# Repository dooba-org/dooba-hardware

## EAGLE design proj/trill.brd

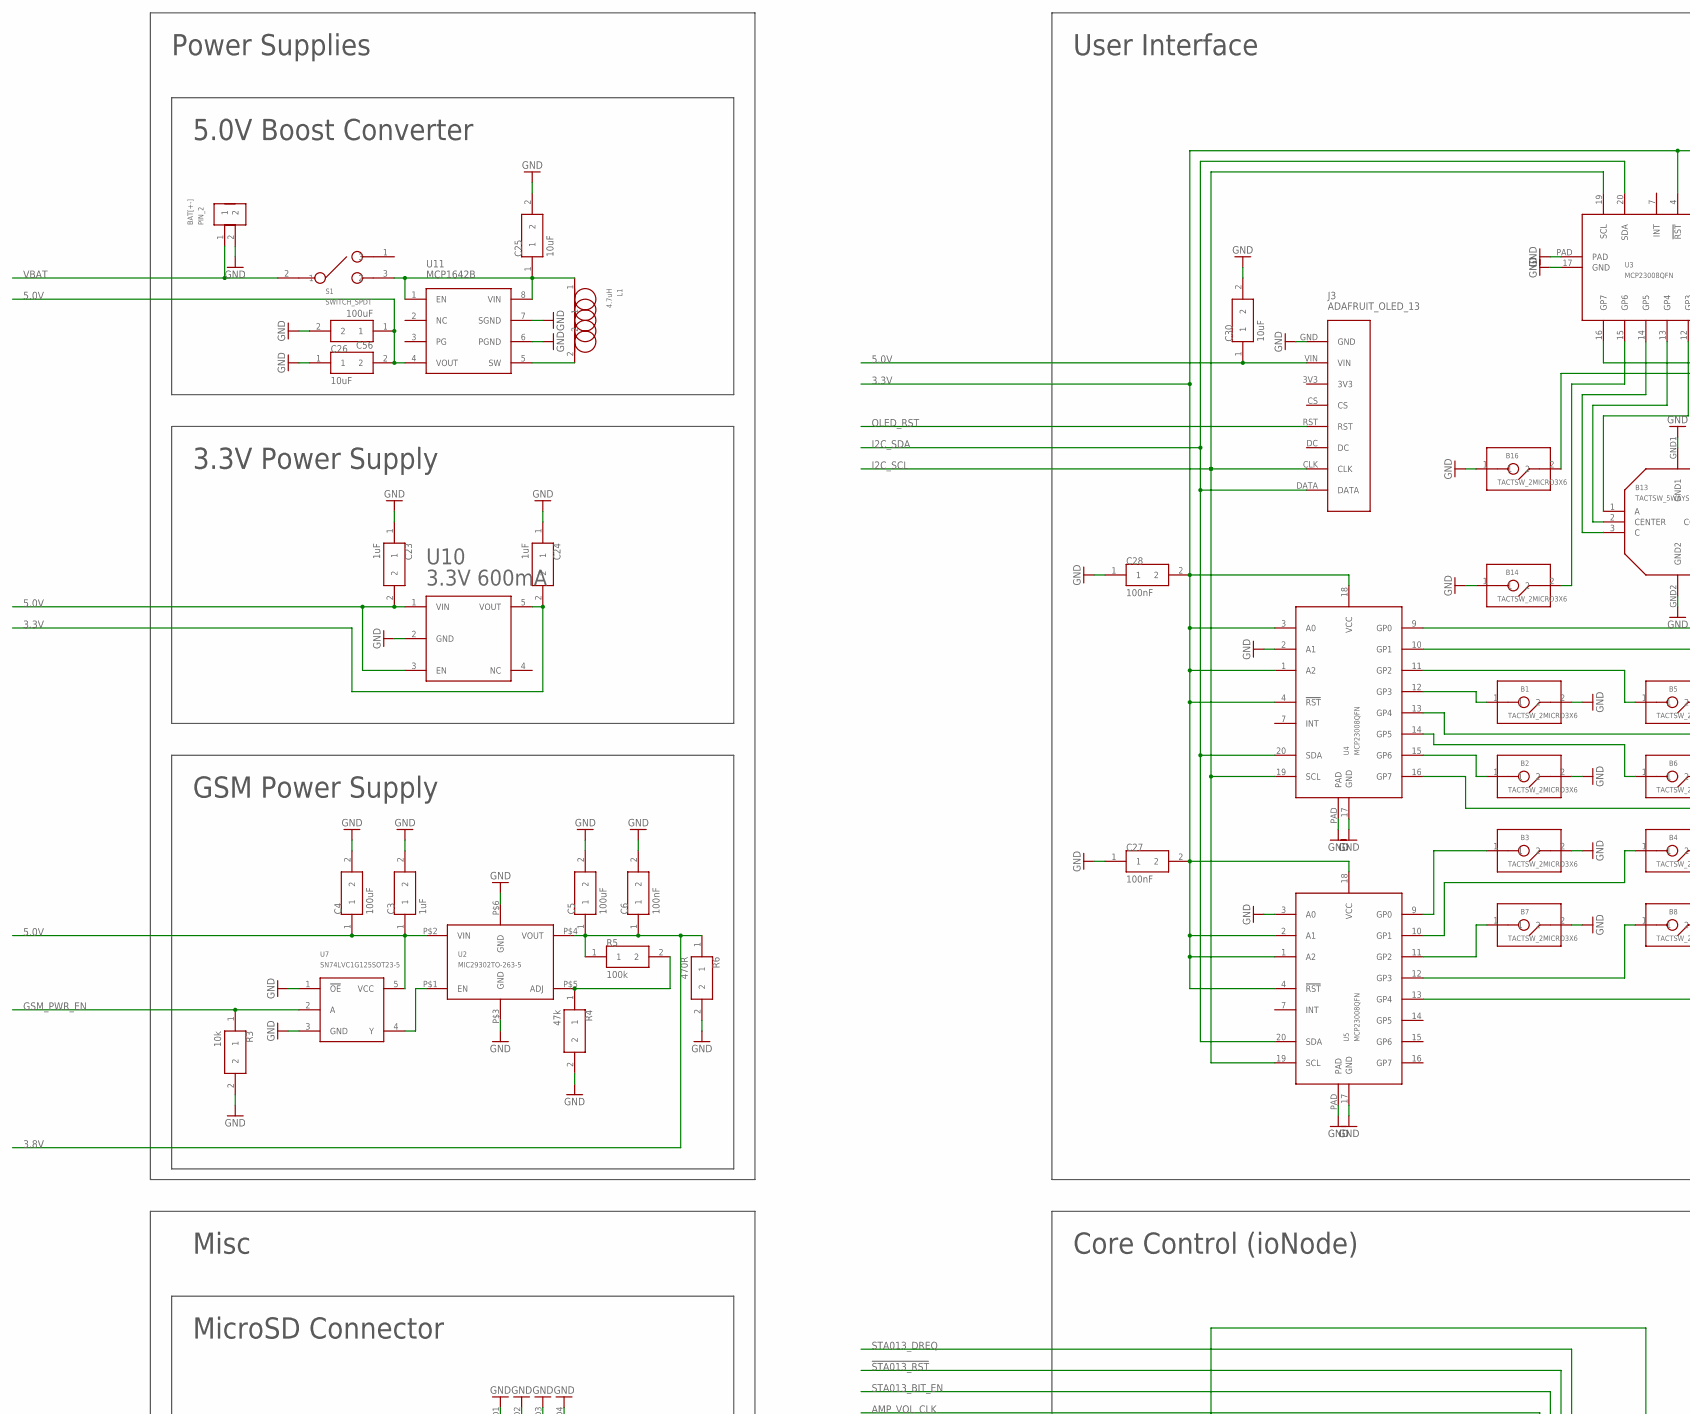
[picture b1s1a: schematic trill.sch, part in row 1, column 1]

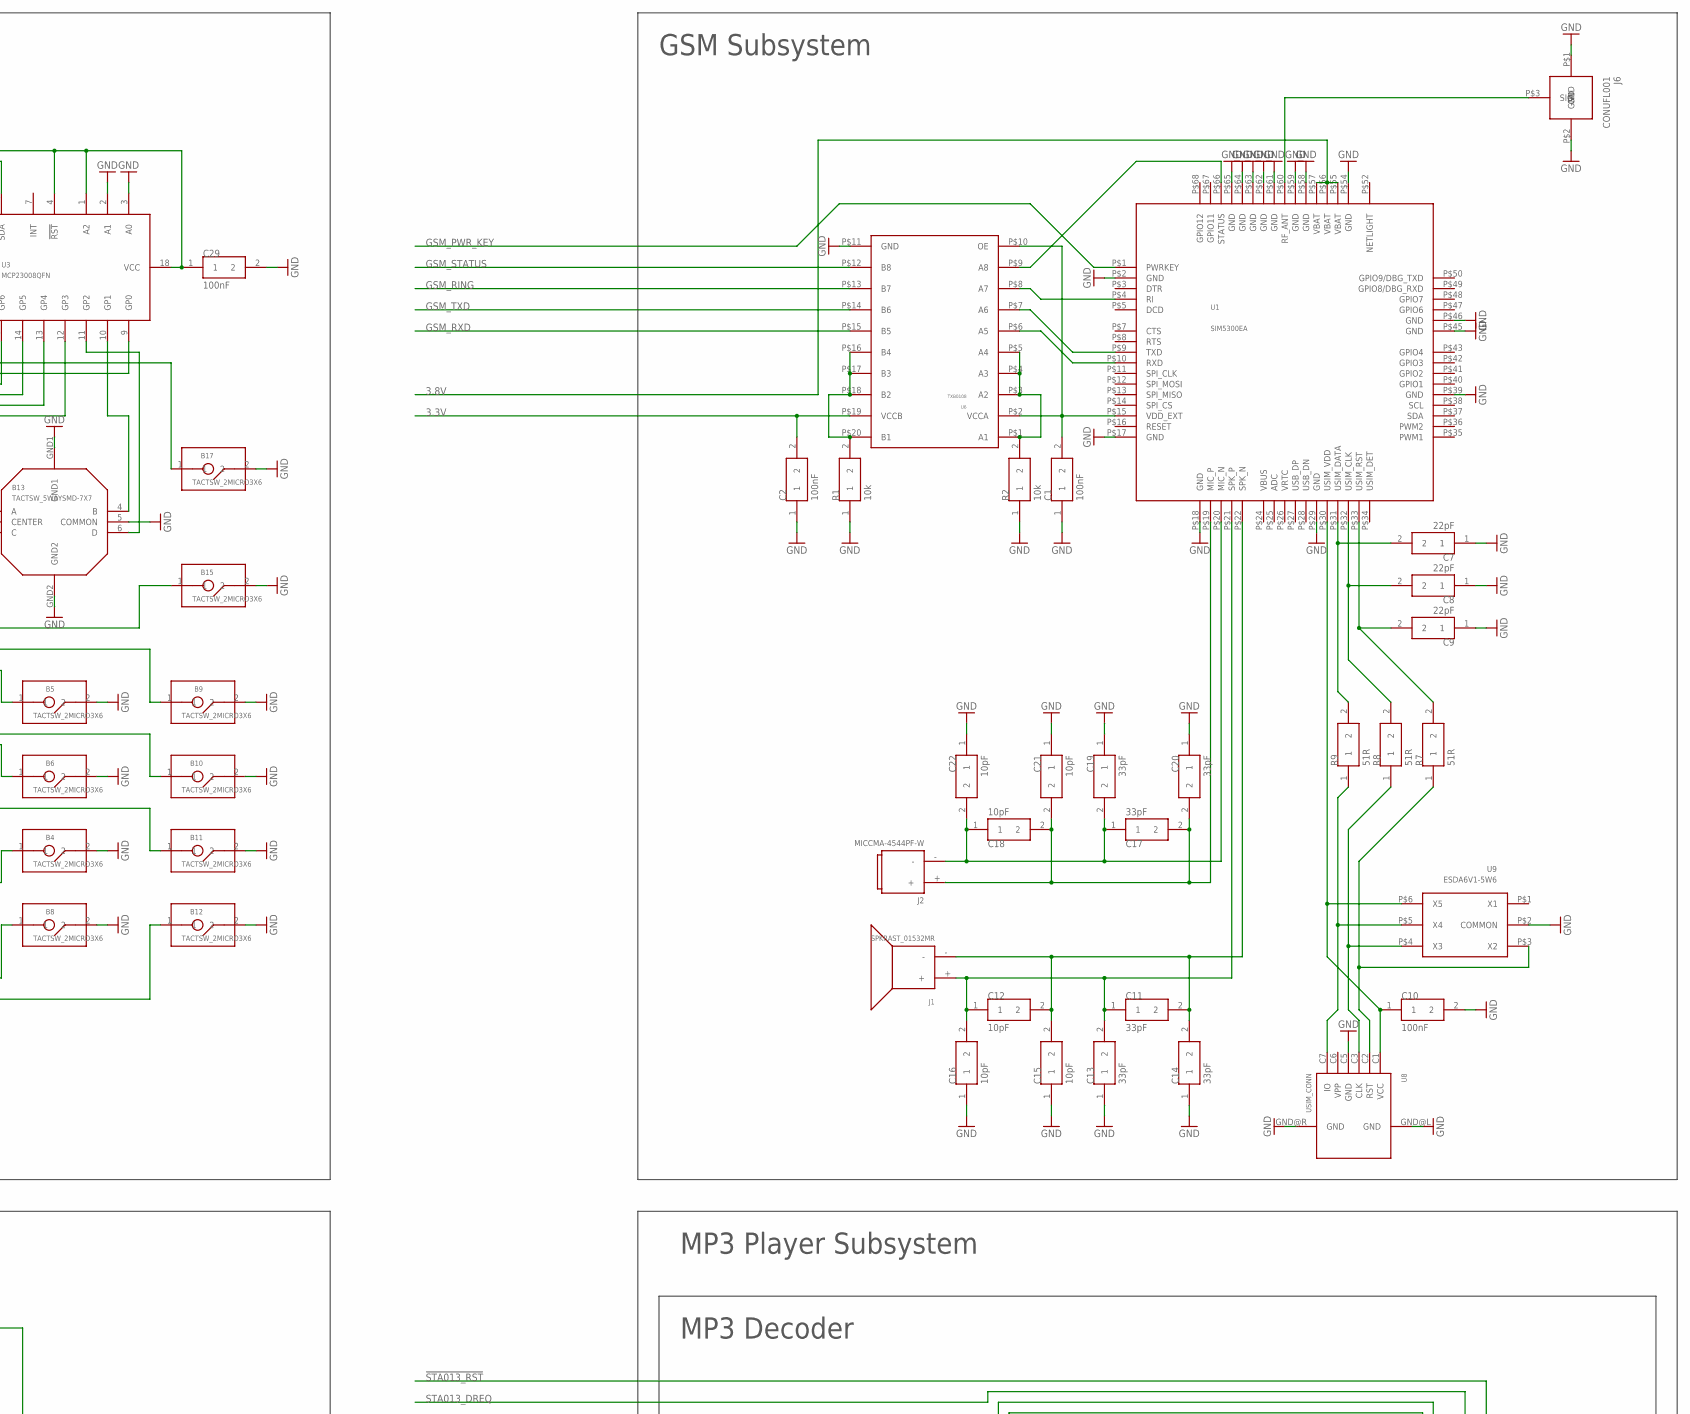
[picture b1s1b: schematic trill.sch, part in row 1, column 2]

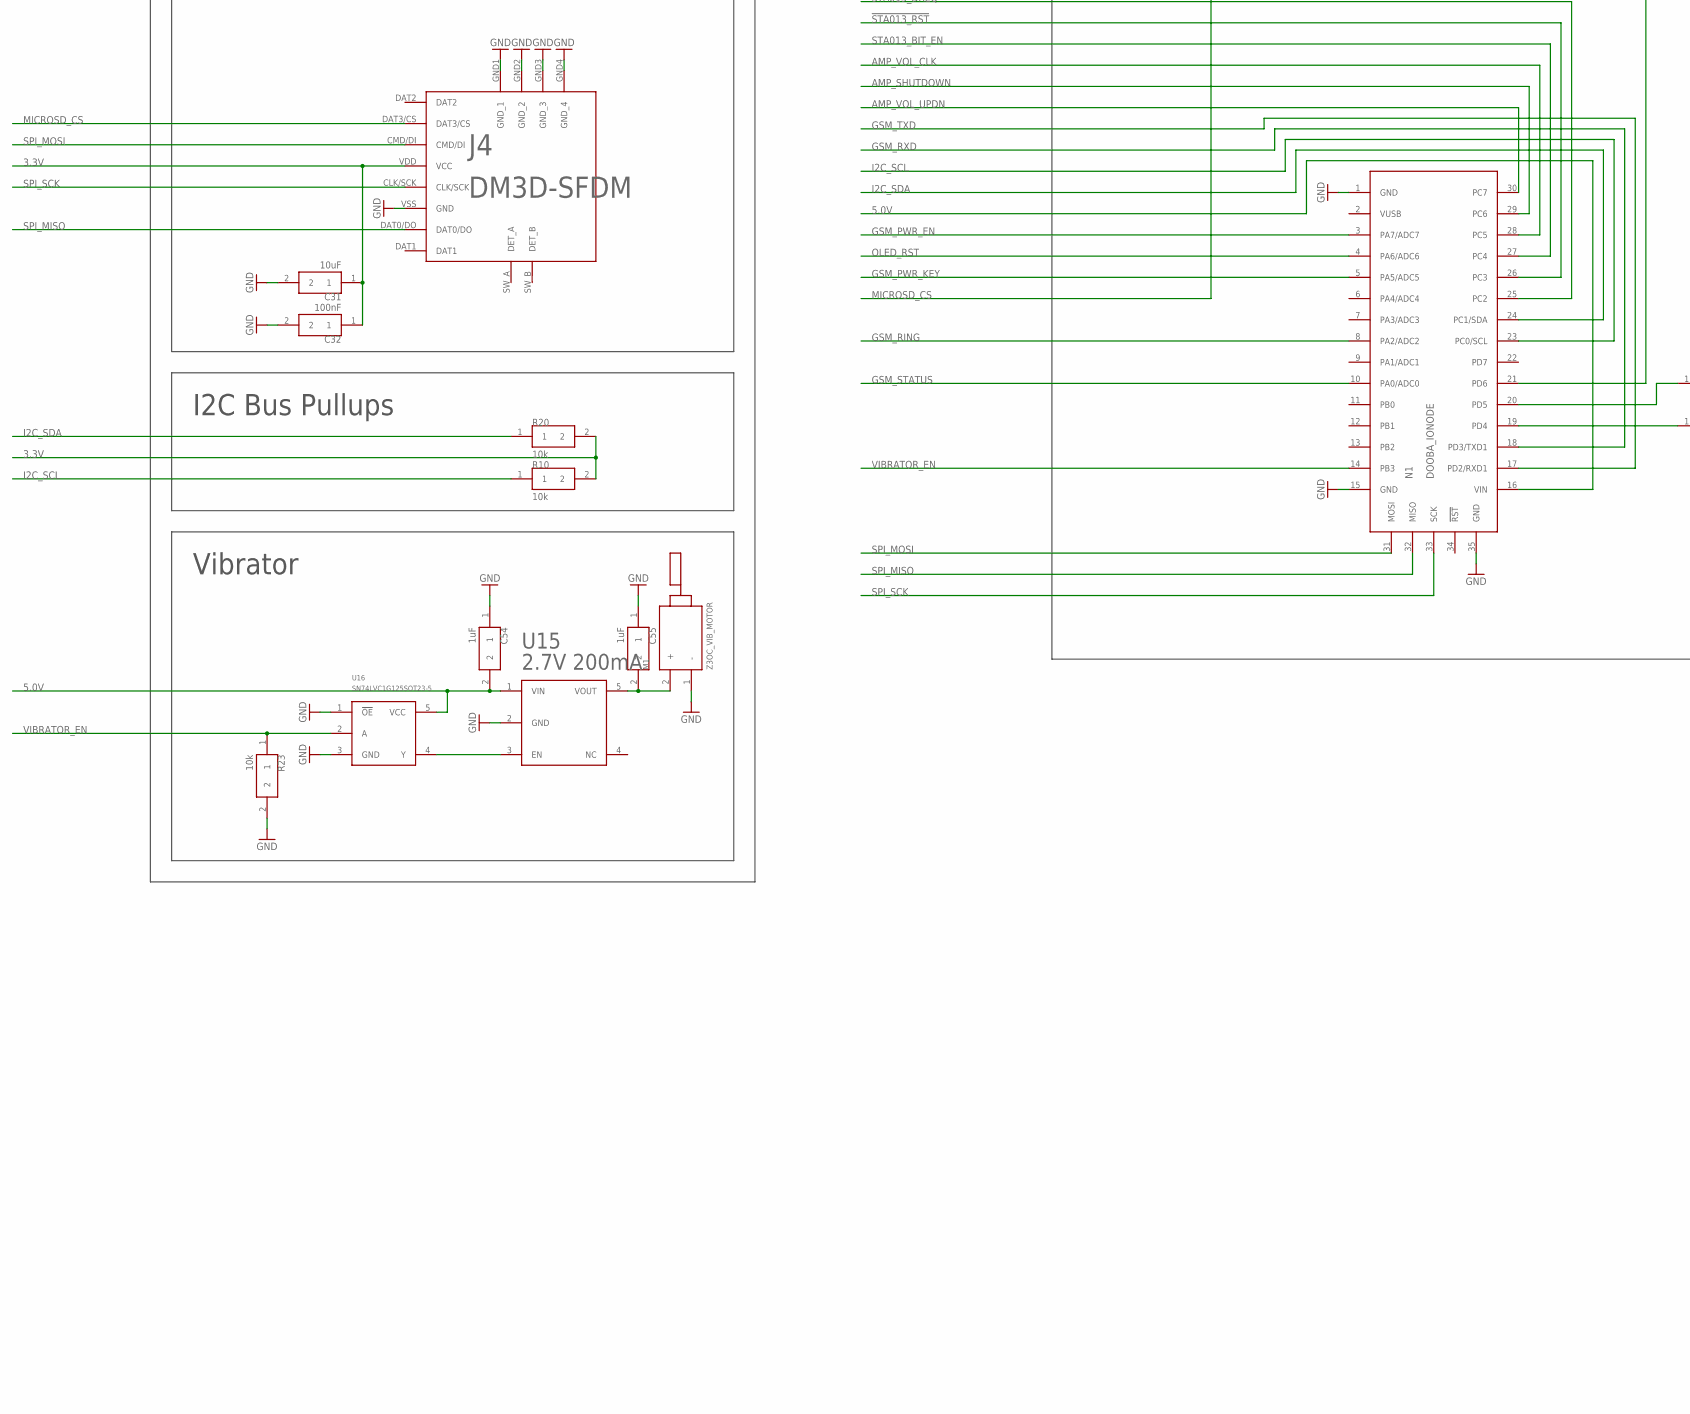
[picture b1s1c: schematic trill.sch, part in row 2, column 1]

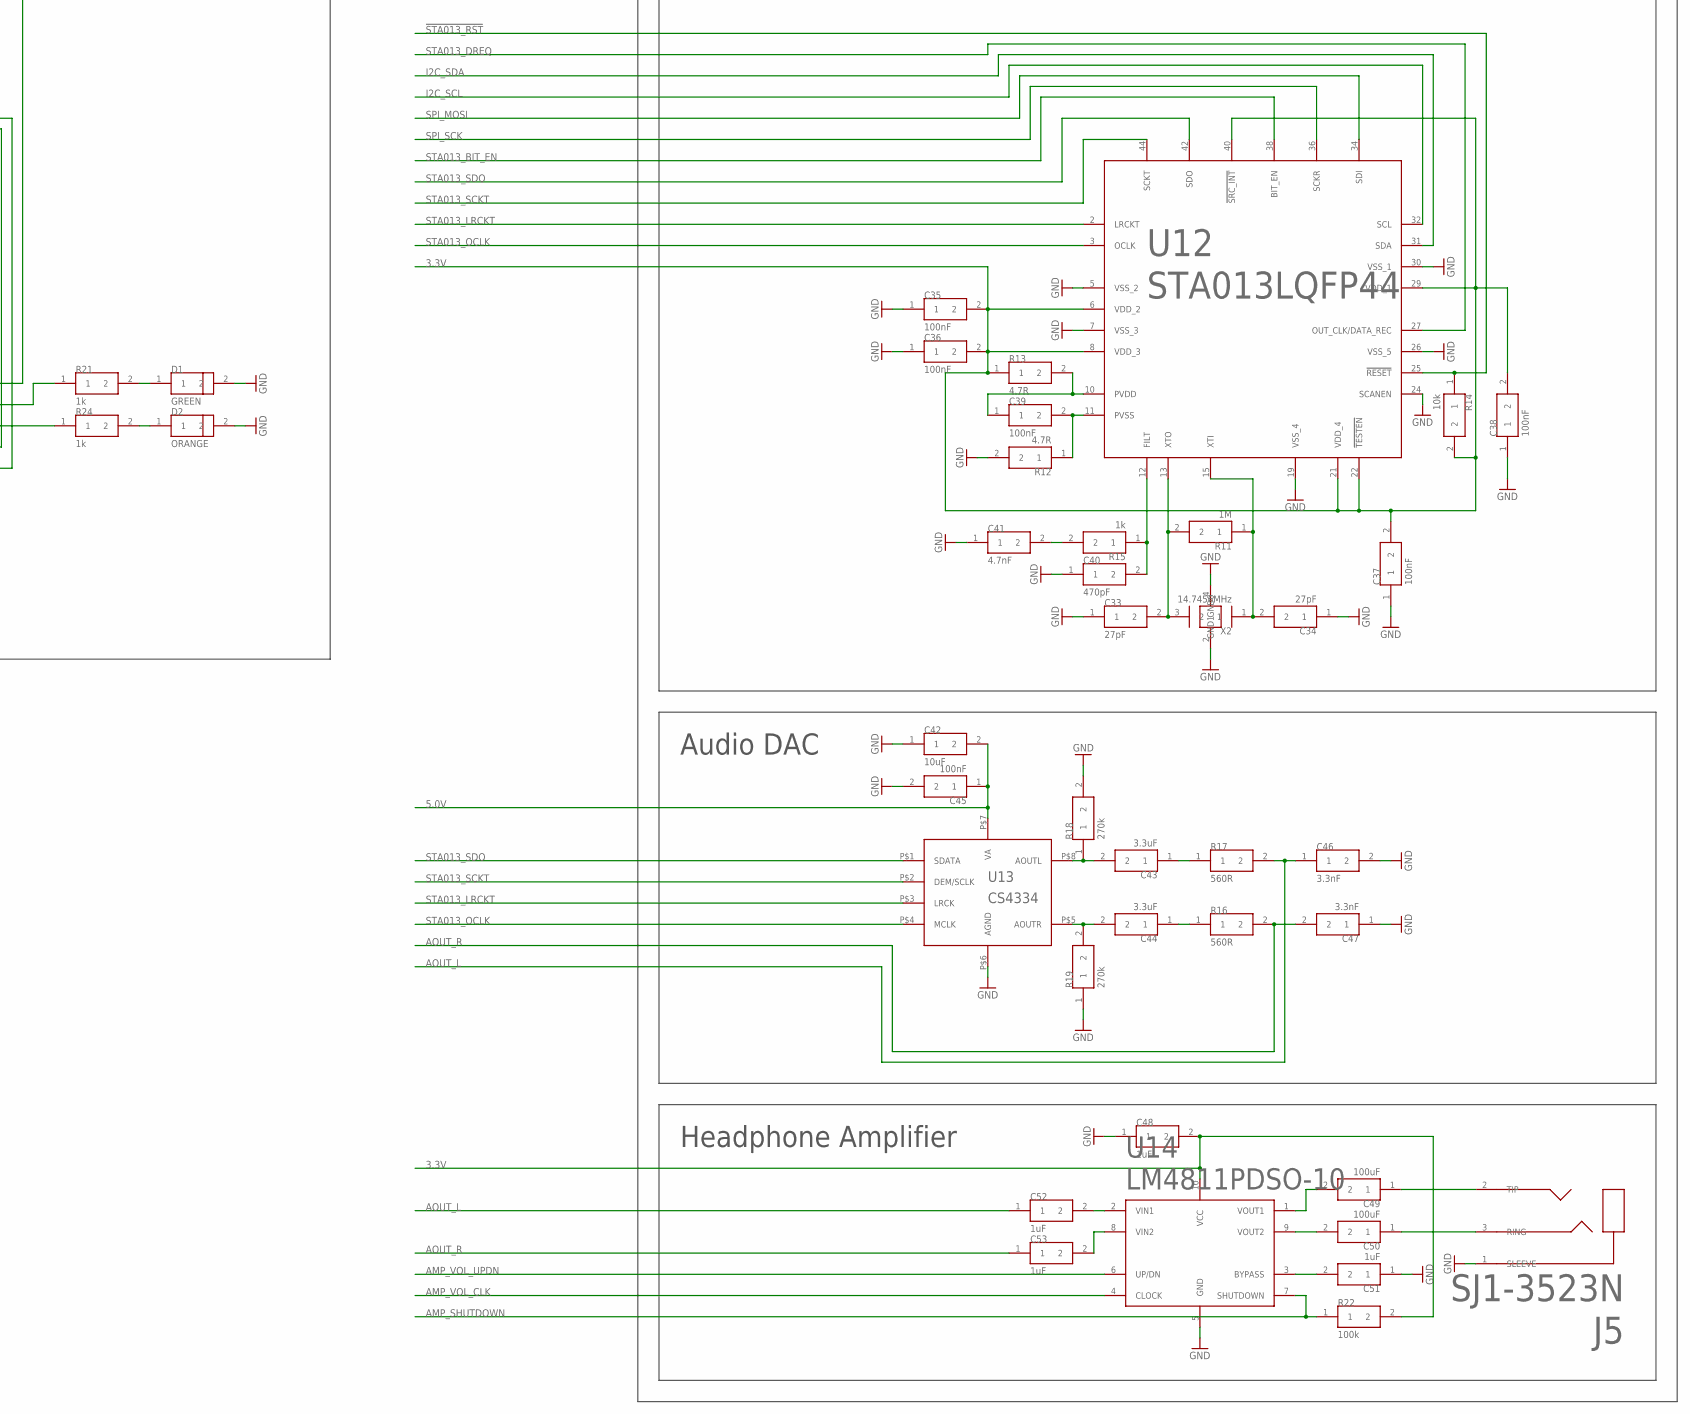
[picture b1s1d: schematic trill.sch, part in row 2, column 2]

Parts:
B1, B2, B3, B4, B5, B6, B7, B8, B9, B10, B11, B12, B14, B15, B16, B17: TACTSW_2MICRO3X6; TACTSW_MICRO3X6
B13: TACTSW_5WAYSMD-7X7; TACTSW-5WAY-7X7
BAT[+-]: PIN_2
C1, C2, C6, C10, C27, C28, C29, C32, C35, C36, C37, C38, C39, C45: 100nF; 0805
C3, C23, C24, C48, C51, C52, C53, C54, C55: 1uF; 0805
C4, C5, C49, C50, C56: 100uF; 1210
C7, C8, C9: 22pF; 0805
C11, C13, C14, C17, C19, C20: 33pF; 0805
C12, C15, C16, C18, C21, C22: 10pF; 0805
C25, C26, C30, C31, C42: 10uF; 0805
C33, C34: 27pF; 0805
C40: 470pF; 0805
C41: 4.7nF; 0805
C43, C44: 3.3uF; 0805
C46, C47: 3.3nF; 0805
D1: GREEN; 0805
D2: ORANGE; 0805
J1: SPKRAST_01532MR; SPKR_AST_01532MR
J2: MICCMA-4544PF-W; MIC_CMA-4544PF-W
J3: ADAFRUIT_OLED_13
J4: DM3D-SFDM; DM3D-SF
J5: SJ1-3523N; SJ1-352XN
J6: CONUFL001
L1: 4.7uH; 2520
M1: Z3OC_VIB_MOTOR
N1: DOOBA_IONODE
R1, R2, R3, R10, R14, R20, R23: 10k; 0805
R4: 47k; 0805
R5, R22: 100k; 0805
R6: 470R; 0805
R7, R8, R9: 51R; 0805
R11: 1M; 0805
R12, R13: 4.7R; 0805
R15, R21, R24: 1k; 0805
R16, R17: 560R; 0805
R18, R19: 270k; 0805
S1: SWITCH_SPDT; JS102011
U1: SIM5300EA; SIM5300
U2: MIC29302TO-263-5; TO-263
U3, U4, U5: MCP23008QFN; 20-VQFN
U6: TXB0108; TSSOP-20
U7, U16: SN74LVC1G125SOT23-5; SOT23-5
U8: USIM_CONN; WE_USIM_HINGE
U9: ESDA6V1-5W6; SOT-323-6L
U10: 3.3V 600mA; SOT23-5
U11: MCP1642B; MSOP8
U12: STA013LQFP44; QFP44
U13: CS4334; SO8
U14: LM4811PDSO-10; PDSO-10
U15: 2.7V 200mA; SOT23-5
X2: 14.7456MHz; XTAL_3225

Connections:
2.7V: C55.2, M1.2 (+), U15.5 (VOUT)
3.3V: C2.2, C24.2, C27.2, C28.2, C29.1, C31.1, C32.1, C35.2, C36.2, C37.2, C38.2, C48.2, J4.VDD (VCC), R10.2, R13.1, R14.2, R20.2, R22.2, U3.1 (A2), U3.4 (!RST), U3.18 (VCC), U4.1 (A2), U4.3 (A0), U4.4 (!RST), U4.18 (VCC), U5.1 (A2), U5.2 (A1), U5.4 (!RST), U5.18 (VCC), U6.P$19 (VCCB), U10.5 (VOUT), U12.6 (VDD_2), U12.8 (VDD_3), U12.21 (VDD_4), U12.22 (!TESTEN), U12.29 (VDD_1), U12.40 (!SRC_INT), U14.10 (VCC)
3.8V: C5.1, C6.1, R5.1, R6.1, U1.P$55 (VBAT), U1.P$56 (VBAT), U1.P$57 (VBAT), U2.P$4 (VOUT)
5.0V: C3.1, C4.1, C23.2, C26.2, C30.1, C42.2, C45.1, C54.2, C56.1, J3.VIN, N1.16 (VIN), U2.P$2 (VIN), U7.5 (VCC), U10.1 (VIN), U10.3 (EN), U11.4 (VOUT), U13.P$7 (VA), U15.1 (VIN), U16.5 (VCC)
!STA013_RST: N1.26 (PC3), R14.1, U12.25 (!RESET)
AMP_SHUTDOWN: N1.29 (PC6), R22.1, U14.7 (SHUTDOWN)
AMP_VOL_CLK: N1.28 (PC5), U14.4 (CLOCK)
AMP_VOL_UPDN: N1.30 (PC7), U14.6 (UP/DN)
AOUT_L: C46.1, C52.1, R17.2
AOUT_R: C47.2, C53.1, R16.2
GND: B1.2, B2.2, B3.2, B4.2, B5.2, B6.2, B7.2, B8.2, B9.2, B10.2, B11.2, B12.2, B13.5 (COMMON), B13.GND1, B13.GND2, B14.1, B15.2, B16.1, B17.2, BAT[+-].2, C1.1, C2.1, C3.2, C4.2, C5.2, C6.2, C7.1, C8.1, C9.1, C10.2, C13.1, C14.1, C15.1, C16.1, C19.1, C20.1, C21.1, C22.1, C23.1, C24.1, C25.2, C26.1, C27.1, C28.1, C29.2, C30.2, C31.2, C32.2, C33.1, C34.1, C35.1, C36.1, C37.1, C38.1, C40.1, C41.1, C42.1, C45.2, C46.2, C47.1, C48.1, C51.1, C54.1, C55.1, C56.2, D1.2, D2.2, J3.GND, J4.GND1 (GND_1), J4.GND2 (GND_2), J4.GND3 (GND_3), J4.GND4 (GND_4), J4.VSS (GND), J5.1 (SLEEVE), J6.P$1 (GND), J6.P$2 (GND), M1.1 (-), N1.1 (GND), N1.15 (GND), N1.35 (GND), R1.1, R2.1, R3.2, R4.2, R6.2, R12.2, R18.2, R19.1, R23.2, U1.P$2 (GND), U1.P$17 (GND), U1.P$18 (GND), U1.P$29 (GND), U1.P$39 (GND), U1.P$45 (GND), U1.P$46 (GND), U1.P$54 (GND), U1.P$58 (GND), U1.P$59 (GND), U1.P$61 (GND), U1.P$62 (GND), U1.P$63 (GND), U1.P$64 (GND), U1.P$65 (GND), U2.P$3 (GND), U2.P$6 (GND), U3.2 (A1), U3.3 (A0), U3.17 (GND), U3.PAD, U4.2 (A1), U4.17 (GND), U4.PAD, U5.3 (A0), U5.17 (GND), U5.PAD, U6.P$11 (GND), U7.1 (!OE), U7.3 (GND), U8.C5 (GND), U8.GND@L (GND), U8.GND@R (GND), U9.P$2 (COMMON), U10.2 (GND), U11.6 (PGND), U11.7 (SGND), U12.5 (VSS_2), U12.7 (VSS_3), U12.19 (VSS_4), U12.24 (SCANEN), U12.26 (VSS_5), U12.30 (VSS_1), U13.P$6 (AGND), U14.5 (GND), U15.2 (GND), U16.1 (!OE), U16.3 (GND), X2.2 (GND0), X2.4 (GND1)
GSM_PWR_EN: N1.3 (PA7/ADC7), R3.1, U7.2 (A)
GSM_PWR_KEY: N1.5 (PA5/ADC5), U1.P$1 (PWRKEY)
GSM_RING: N1.8 (PA2/ADC2), U6.P$13 (B7)
GSM_RXD: N1.18 (PD3/TXD1), U6.P$15 (B5)
GSM_STATUS: N1.10 (PA0/ADC0), U6.P$12 (B8)
GSM_TXD: N1.17 (PD2/RXD1), U6.P$14 (B6)
I2C_SCL: J3.CLK, N1.23 (PC0/SCL), R10.1, U3.19 (SCL), U4.19 (SCL), U5.19 (SCL), U12.32 (SCL)
I2C_SDA: J3.DATA, N1.24 (PC1/SDA), R20.1, U3.20 (SDA), U4.20 (SDA), U5.20 (SDA), U12.31 (SDA)
MICROSD_CS: J4.DAT3/CS, N1.21 (PD6)
unnamed: B13.4 (B), U3.10 (GP1)
unnamed: B13.1 (A), U3.12 (GP3)
unnamed: B13.2 (CENTER), U3.13 (GP4)
unnamed: B13.3 (C), U3.14 (GP5)
unnamed: B13.6 (D), U3.11 (GP2)
unnamed: B14.2, U3.15 (GP6)
unnamed: B16.2, U3.9 (GP0)
unnamed: B17.1, U3.16 (GP7)
unnamed: B15.1, U4.9 (GP0)
unnamed: B9.1, U4.10 (GP1)
unnamed: B5.1, U4.11 (GP2)
unnamed: B1.1, U4.12 (GP3)
unnamed: B10.1, U4.13 (GP4)
unnamed: B6.1, U4.14 (GP5)
unnamed: B2.1, U4.15 (GP6)
unnamed: B11.1, U4.16 (GP7)
unnamed: B3.1, U5.9 (GP0)
unnamed: B4.1, U5.10 (GP1)
unnamed: B7.1, U5.11 (GP2)
unnamed: B8.1, U5.12 (GP3)
unnamed: B12.1, U5.13 (GP4)
unnamed: C1.2, U1.P$15 (VDD_EXT), U6.P$2 (VCCA), U6.P$10 (OE)
unnamed: U1.P$66 (STATUS), U6.P$9 (A8)
unnamed: U1.P$4 (RI), U6.P$8 (A7)
unnamed: U1.P$9 (TXD), U6.P$7 (A6)
unnamed: U1.P$10 (RXD), U6.P$6 (A5)
unnamed: U2.P$1 (EN), U7.4 (Y)
unnamed: R4.1, R5.2, U2.P$5 (ADJ)
unnamed: R1.2, U6.P$16 (B4), U6.P$17 (B3), U6.P$18 (B2), U6.P$20 (B1)
unnamed: C10.1, U1.P$30 (USIM_VDD), U8.C1 (VCC), U9.P$6 (X5)
unnamed: R2.2, U6.P$1 (A1), U6.P$3 (A2), U6.P$4 (A3), U6.P$5 (A4)
unnamed: R9.1, U8.C7 (IO), U9.P$5 (X4)
unnamed: R8.1, U8.C3 (CLK), U9.P$4 (X3)
unnamed: C34.2, R11.1, U12.15 (XTI), X2.1
unnamed: R7.1, U8.C2 (RST), U9.P$3 (X2)
unnamed: C9.2, R7.2, U1.P$33 (USIM_RST)
unnamed: C8.2, R8.2, U1.P$32 (USIM_CLK)
unnamed: C7.2, R9.2, U1.P$31 (USIM_DATA)
unnamed: C33.2, R11.2, U12.13 (XTO), X2.3 (2)
unnamed: L1.2, U11.5 (SW)
unnamed: C39.1, R13.2, U12.10 (PVDD)
unnamed: C11.2, C12.2, C14.2, C15.2, J1.-, U1.P$22 (SPK_N)
unnamed: C11.1, C12.1, C13.2, C16.2, J1.+, U1.P$21 (SPK_P)
unnamed: C39.2, R12.1, U12.11 (PVSS)
unnamed: C41.2, R15.2
unnamed: C17.2, C18.2, C20.2, C21.2, J2.+, U1.P$19 (MIC_P)
unnamed: C17.1, C18.1, C19.2, C22.2, J2.-, U1.P$20 (MIC_N)
unnamed: C40.2, R15.1, U12.12 (FILT)
unnamed: C43.2, R18.1, U13.P$8 (AOUTL)
unnamed: C44.2, R19.2, U13.P$5 (AOUTR)
unnamed: C44.1, R16.1
unnamed: C43.1, R17.1
unnamed: C49.2, U14.1 (VOUT1)
unnamed: C50.2, U14.9 (VOUT2)
unnamed: C51.2, U14.3 (BYPASS)
unnamed: C50.1, J5.3 (RING)
unnamed: C52.2, U14.2 (VIN1)
unnamed: C53.2, U14.8 (VIN2)
unnamed: C49.1, J5.2 (TIP)
unnamed: J6.P$3 (SIG), U1.P$60 (RF_ANT)
unnamed: U15.3 (EN), U16.4 (Y)
unnamed: D1.1, R21.2
unnamed: D2.1, R24.2
unnamed: N1.19 (PD4), R24.1
unnamed: N1.20 (PD5), R21.1
OLED_RST: J3.RST, N1.4 (PA6/ADC6)
SPI_MISO: J4.DAT0/DO, N1.32 (MISO)
SPI_MOSI: J4.CMD/DI, N1.31 (MOSI), U12.34 (SDI)
SPI_SCK: J4.CLK/SCK, N1.33 (SCK), U12.36 (SCKR)
STA013_BIT_EN: N1.27 (PC4), U12.38 (BIT_EN)
STA013_DREQ: N1.25 (PC2), U12.27 (OUT_CLK/DATA_REC)
STA013_LRCKT: U12.2 (LRCKT), U13.P$3 (LRCK)
STA013_OCLK: U12.3 (OCLK), U13.P$4 (MCLK)
STA013_SCKT: U12.44 (SCKT), U13.P$2 (DEM/SCLK)
STA013_SDO: U12.42 (SDO), U13.P$1 (SDATA)
VBAT: BAT[+-].1, S1.2 (1)
VIBRATOR_EN: N1.14 (PB3), R23.1, U16.2 (A)
VIN: C25.1, L1.1, S1.3 (2), U11.1 (EN), U11.8 (VIN)

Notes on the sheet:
GSM Power Supply
3.3V Power Supply
5.0V Boost Converter
Power Supplies
User Interface
GSM Subsystem
Headphone Amplifier
Audio DAC
MP3 Decoder
MP3 Player Subsystem
MicroSD Connector
I2C Bus Pullups
Core Control (ioNode)
Misc
Vibrator

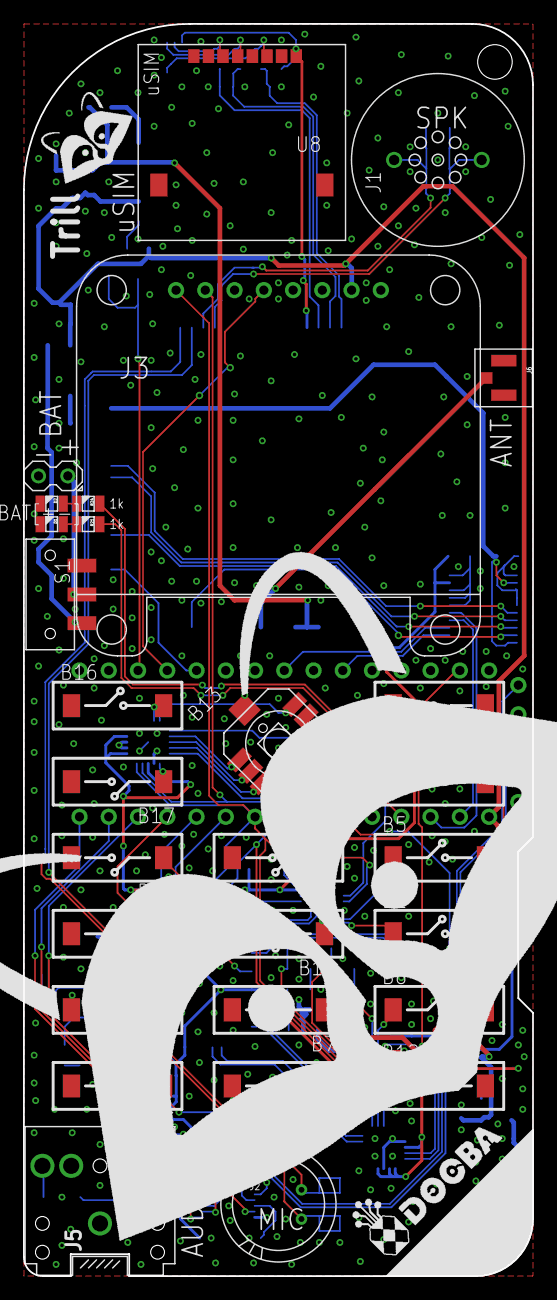
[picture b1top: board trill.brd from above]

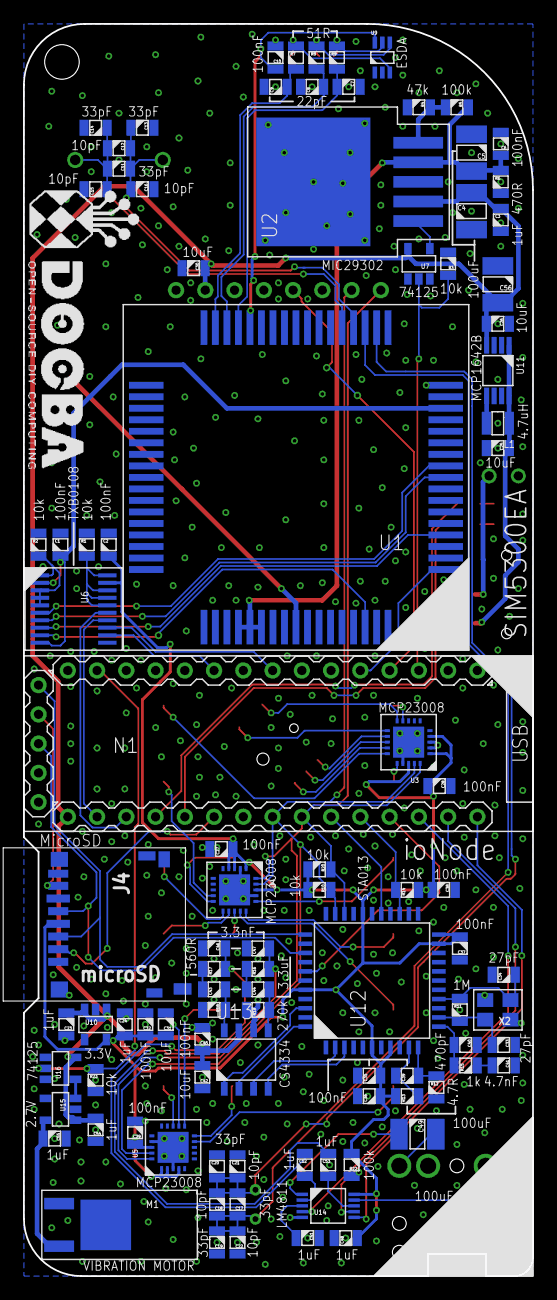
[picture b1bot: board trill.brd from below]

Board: 2 copper layers, 44.2 x 108.7 mm, 127 parts (98 on the bottom side), 98 nets.
